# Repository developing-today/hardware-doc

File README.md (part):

# Hardware research

Standalone repository: **[`developing-today/hardware-doc`](https://github.com/developing-today/hardware-doc)**.

Device and component research, decomposed to primary evidence — netlists parsed from vendor
EDA files, firmware images unpacked, datasheets mined — with every claim carrying its source
and evidence status.

## How this repo is used

It is normally checked out **beside** the repo that consumes it and symlinked into place:

```
<repo-parent>/
├── code/                        consuming repo (config, infra, …)
│   └── doc/hardware  ───────────┐ symlink, created by scripts/hardware-doc-init.sh
├── hardware-doc/         ←──────┘ THIS REPO
└── repo-archive/        bulk artifacts moved out of here (separate repo, usually unpublished)
```

It is **not a submodule and not vendored** into the consuming repo: at ~440 MB it would
make every clone of that repo roughly 6.5× larger. Consumers clone it on demand.

```bash
git clone https://github.com/developing-today/hardware-doc.git
./scripts/init.sh        # only needed if the archive is not already a sibling
```

`scripts/init.sh` points `archive/` and `scratch/` at the sibling artifact archive. A fresh
clone usually needs nothing — the symlinks are committed relative, so they already resolve when
`repo-archive/` sits beside this repo. Run it when the archive is elsewhere, newly added, or
this repo is a linked worktree. It never clones and never deletes.

### Resolving the sibling archive

`../repo-archive` is a sibling of the **real repository root** — not of your working
directory, and not `~`. Under a git worktree resolve it via the *common* dir:

```bash
ARCHIVE="$(dirname "$(dirname "$(git rev-parse --path-format=absolute --git-common-dir)")")/repo-archive"
```

`--git-common-dir` rather than `--show-toplevel`: inside a linked worktree the toplevel is the
worktree, whose parent is the wrong directory. The archive holds bulky derived artifacts moved
out of this repo; every one leaves a `*.ARCHIVED.md` placeholder here carrying size, SHA-256,
upstream commit/author/licence and multiple recovery URLs, so **the archive is optional** —
its absence costs you convenience, not information.

`repo-archive` is **itself a git repository**, but it is normally **unpublished or
private** — at multiple gigabytes it is impractical to host alongside this one. Treat it as a
local companion: if you have it, placeholders resolve to real bytes; if you do not, they
resolve to recovery URLs.

### The `archive/` symlink

When the archive is present locally it is reachable at **`./archive/`** — a tracked symlink
into the `../repo-archive` repository. That gives `*.ARCHIVED.md` placeholders a stable in-repo
path to point at.

⚠ It resolves to **`../repo-archive/hardware-doc`** — the subdirectory named after **this
repository** — not to the archive root. `repo-archive` serves any sibling repo and namespaces
everything by source repo name, so the general form is `../repo-archive/<reponame>`; `scratch`
follows the same rule at `../repo-archive/scratch/<reponame>`.

So `archive/components/…` maps to `repo-archive/hardware-doc/components/…`, and a link written
`archive/hardware-doc/…` repeats the segment and **will not resolve** — silently, since a Markdown
link to a missing path just points at nothing.

Both tracked symlinks in this project (`archive` here, `doc/hardware` in a consuming repo)
are committed **relative**, and `hardware-doc-init.sh` swaps in an **absolute** path only
where the relative form cannot resolve — then marks the path `--skip-worktree`, because
`.gitignore` has no effect on tracked files. See
[`AGENTS.md` § Symlinks and `--skip-worktree`](AGENTS.md#symlinks-and---skip-worktree) for
the caveat that matters: while the flag is set, git will not update that path.

See [`AGENTS.md`](AGENTS.md) for working conventions and
[`.agents/skills/hardware-device-research/SKILL.md`](.agents/skills/hardware-device-research/SKILL.md)
for the research method.

- [Devices](devices/README.md)
- [Components and interfaces](components/README.md)
- [Vendor documentation-sourcing guides](vendors/README.md)
- [Cross-cutting guides](guides/README.md) — [Espressif](guides/espressif/README.md) · [hardware subsystems](guides/hardware/README.md) · [NFC](guides/nfc/README.md) · [LoRa](guides/lora/README.md) · [markets and sourcing](guides/markets/README.md) · [reverse engineering](guides/reverse-engineering/netlists-from-vendor-eda-files.md) · [research technique](guides/research/finding-projects-that-use-a-board.md) · [NixOS host](guides/nixos/README.md)
- [Artifact manifest](artifact-manifest.md)
- [Inventory](inventory.txt)
- [Verification report](verification.json)
- [Component download failures](component-download-failures.txt)

All research in this initial set was retrieved 2026-08-21. Downloaded files are checksummed from local bytes; see each device/component record for provenance and caveats. Relative-link validation covers authored Markdown outside `artifacts/`; bundled upstream Markdown is preserved as supplied and is not claimed to be link-clean.

- [Size audit](SIZE-AUDIT.md) — where the 442 MB is, what is reproducible, what must stay

## Research passes

| Pass | Date | Scope |
|---|---|---|
| Waveshare ESP32-S3-Knob-Touch-LCD-1.8 | 2026-08-21 → 2026-08-23 | One device, decomposed into ~22 component records; Espressif and Waveshare vendor guides created |
| Framework-guide extraction and archival | 2026-08-24 | Distilled ESP-IDF (×5 target builds), ESP-ADF, ESP-IoT-Solution and esp-dev-kits PDFs into [`guides/espressif/`](guides/espressif/README.md), then archived the ~219 MB of regenerable framework PDFs out of the repository. Chip datasheets, TRMs, errata, hardware-design guidelines and board design files were **all retained**. Per-directory archive records with SHA-256 and verified download URLs: [u4wdh](components/espressif/esp32-u4wdh/artifacts/ARCHIVED-FRAMEWORK-GUIDES.md) · [s3r8](components/espressif/esp32-s3r8/artifacts/ARCHIVED-FRAMEWORK-GUIDES.md) · [p4](components/espressif/esp32-p4/artifacts/ARCHIVED-FRAMEWORK-GUIDES.md) · [P4 boards](devices/espressif/shared-artifacts/ARCHIVED-FRAMEWORK-GUIDES.md) |
| **Espressif ESP32-P4 and its official development boards** | **2026-08-21** | [ESP32-P4 component record](components/espressif/esp32-p4/README.md) plus **five** board records under [devices/espressif/](devices/espressif/). Established the real P4 board lineup (no Korvo board exists on P4); corrected three claims in the [Espressif vendor guide](vendors/espressif/README.md#8-change-log-for-this-guide) |
| **Cross-link completion, vendor guides and market docs** | **2026-08-24** | **17 new [vendor sourcing guides](vendors/README.md)** (10 for manufacturers whose parts we document, 7 anticipatory), each with product lines, part-numbering conventions, distribution channels, URL patterns verified by live probe **with negative controls**, and an explicit evidence boundary. Added manufacturer back-links to every manufacturer-specific component record. New [markets and sourcing](guides/markets/README.md) guides and the [Espressif ecosystem map](guides/espressif/ecosystem-and-product-lines.md). **Corrected a WCH finding**: the `downloads/<PART>DS1_PDF.html` URLs return an identical 4,305-byte SPA shell for every path, existing or not |
| **Host toolchain: NixOS embedded development** | **2026-08-30** | New [`guides/nixos/`](guides/nixos/README.md) covering ESP-IDF on NixOS (5.5.2 and 6.0.1 side by side, and why installing the package alone yields no `idf.py`), package availability in the locked nixpkgs with dated absences, and why LVGL/sensor libraries are project dependencies. New [SquareLine vendor guide](vendors/squareline/README.md) — the Linux build is **a ZIP, not an AppImage**, and the CDN **returns HTTP 206 for non-existent paths**. The 172 MiB proprietary editor ZIP is archived out of the repository with a [reacquisition record](vendors/squareline/artifacts/ARCHIVED-SQUARELINE-STUDIO-LINUX.md). ⚠ **Nothing in this pass was built or rebuilt** |
| **Seven-session sweep: Xteink, M5Stack DinMeter / Cardputer / LoRa expansions, LilyGO K230 and T-Display-S3, LoRa generations** | **2026-09-04 → 2026-09-07** | ~40 device records and ~90 component records across seven parallel sessions, indexed here on 2026-09-07. New device families: [Xteink](devices/README.md#xteink-阅星瞳--星瞳-star-pupil) pocket e-readers (6), [LilyGO](devices/README.md#lilygo-shenzhen-xin-yuan-electronic-technology-also-trades-as-ttgo) (16, including the repository's **first RISC-V device**, the K230), and the expanded [M5Stack](devices/README.md#m5stack) family — DinMeter ×2, five Cardputers and eight Cardputer radio expansions. Three new vendor guides ([Canaan](vendors/canaan/README.md), [LilyGO](vendors/lilygo/README.md), [Semtech](vendors/semtech/README.md)) and three cross-cutting guides ([LoRa radio generations](guides/hardware/lora-radio-generations.md), [parallel 8080 LCD buses](guides/hardware/parallel-8080-lcd-buses.md), [RISC-V and vendor-SDK toolchains on NixOS](guides/nixos/riscv-and-vendor-sdk-toolchains.md)). ⚠ **Nothing in this pass was verified on physical hardware**, and each session was forbidden from editing shared indexes — the merge, its deferrals and its parked corrections are recorded in [`research/passes/index-merge/README.md`](research/passes/index-merge/README.md) |
| **Round two: Xteink re-survey, schematic net-tracing, certification and market** | **2026-09-11** | Three parallel sessions, integrated the same day. ⭐ **Overturned the sweep's Xteink certification finding**: Xteink holds **five FCC Original Equipment grants** under grantee code `2BTR9`, and enumerating that code surfaced a **sixth device the vendor has never announced** — the [X4 Light](devices/xteink/x4-light/README.md). Dated the **X4 Classic launch** (2026-09-06, USD 79) and the **X4's withdrawal**. **291 schematic PDFs assessed** and five boards net-traced from PDF alone — Altium exports embed `CO`/`PI`/`NL` tokens at item coordinates, which is what made it possible ([guide](guides/reverse-engineering/tracing-nets-from-schematic-pdfs.md)). **32 device records gained a `certification-and-compliance.md`**, each carrying its positive and negative controls. **174 FCC exhibits split**: 59 retained in-repo (57.8 MiB — internal photographs, including the **first public teardown of the Xteink X4**), 106 archived with self-sufficient placeholders (130.6 MiB); FCC exhibits are **US Government public records, redistribution `allowed`**. New guides: [finding certification records](guides/research/finding-certification-records.md), [tracing nets from schematic PDFs](guides/reverse-engineering/tracing-nets-from-schematic-pdfs.md); new [Xteink vendor guide](vendors/xteink/README.md). ⚠ **Still nothing verified on physical hardware.** ⚠ `devices/m5stack/papermono/**` was owned by a live session throughout and was **not touched** — its deferrals are in [`research/passes/index-merge/deferred-round2.md`](research/passes/index-merge/deferred-round2.md) |

| **Preprint repositories and the wider literature** | **2026-09-01 → 2026-09-11** | All 78 entries on Wikipedia's [List of preprint repositories][wpl] **plus what that list omits**, in [`research/preprint-repositories/`](research/preprint-repositories/README.md) — 40 records, ~23,000 lines. Deep records for the servers carrying hardware/software/systems work ([arXiv](research/preprint-repositories/arxiv.md), [Cryptology ePrint](research/preprint-repositories/cryptology-eprint-archive.md), [HAL](research/preprint-repositories/hal.md), [Zenodo](research/preprint-repositories/zenodo.md), [TechRxiv](research/preprint-repositories/techrxiv.md), [ECSarXiv](research/preprint-repositories/ecsarxiv.md)); grouped records for the rest. **160 landmark papers and theses individually verified** by fetching each identifier and machine-checking its title — [collected by field](research/preprint-repositories/landmark-papers.md). ⭐ **Corrected six Wikipedia claims by measurement** (OSF Preprints `>1,000,000` → **200,519** hosted; ScienceOpen → **~3,584**; [Synthical hosts nothing at all](research/preprint-repositories/synthical.md)). Extended beyond preprints to the [lawful full-text ladder](research/preprint-repositories/open-access-full-text-sources.md) (**USENIX has been paywall-free since 2008** — the real home of the systems literature), [government and university technical reports](research/preprint-repositories/government-and-institutional-technical-reports.md) (**the RISC-V ISA specs are six Berkeley EECS reports**, verified), the [computing servers Wikipedia omits](research/preprint-repositories/additional-preprint-servers.md) (**ECCC**, **OpenReview**), [theses and dissertations](research/preprint-repositories/theses-and-dissertations.md) (**the global ETD discovery layer collapsed in 2025–26**; EThOS is metadata-only since the British Library cyberattack), [dead-site recovery](research/preprint-repositories/recovering-dead-technical-sites.md) (**the DEC SRC/WRL/CRL series survives only as a 2007 bitsavers mirror**), and [bulk libraries and their copyright status](research/preprint-repositories/bulk-libraries-and-shadow-archives.md). ⚠ **No artifacts retained; no shadow-library service probed and no mirror domains recorded anywhere** |

[wpl]: https://en.wikipedia.org/wiki/List_of_preprint_repositories

## Quick entry points

- **How do I build firmware from this machine?** — [NixOS as an embedded development host](guides/nixos/README.md)
- **Where is the paper for this, and can I trust it?** — [preprint repositories](research/preprint-repositories/README.md) · [landmark papers by field](research/preprint-repositories/landmark-papers.md) · [reliability and durability](research/preprint-repositories/reliability-and-durability.md)
- **I have a citation and want the PDF, legally** — [open-access full-text ladder](research/preprint-repositories/open-access-full-text-sources.md)
- **A vendor doc portal or datasheet host has died** — [recovering dead technical sites](research/preprint-repositories/recovering-dead-technical-sites.md)

- **Which Espressif chip should this be?** — [ecosystem and product lines](guides/espressif/ecosystem-and-product-lines.md)
- **Which of these boards should I use?** — [device comparison matrix](guides/markets/device-comparison-matrix.md) — all fourteen documented devices side by side
- **How many PCNT units / DMA channels / UARTs does this chip have?** — [SoC peripheral reference](guides/espressif/soc-peripheral-reference.md)
- **How do I drive this display?** — [display interfaces](guides/hardware/display-interfaces.md) · e-paper specifically — [e-paper displays](guides/hardware/e-paper-displays.md)
- **How do I bring up an NFC reader, and why does it read nothing?** — [NFC guide](guides/nfc/README.md) — standards, antenna matching, and symptom-to-cause debugging
- **What do SF, BW and CR actually cost me?** — [LoRa guide](guides/lora/README.md) — airtime, battery and duty-cycle arithmetic, LoRa vs LoRaWAN vs Meshtastic, and honest range estimation
- **Where should I buy this, and will the docs survive?** — [vendor and marketplace comparison](guides/markets/vendor-comparison.md)
- **Is this board a clone, and what differs?** — [clones, siblings and variants](guides/markets/clones-and-variants.md)
- **How do I recover a pinout the vendor never published?** — [netlists from vendor EDA files](guides/reverse-engineering/netlists-from-vendor-eda-files.md)
- **Espressif ESP32-P4** — [chip](components/espressif/esp32-p4/README.md) · [board index](devices/README.md#espressif--official-esp32-p4-development-boards) · [shared board artifacts](devices/espressif/shared-artifacts/README.md)
- **Espressif ESP32-S3** — [ESP32-S3R8](components/espressif/esp32-s3r8/README.md), including the [Bluetooth Classic limitation](components/espressif/esp32-s3r8/README.md#radio-capabilities-and-the-classic-bluetooth-limitation)
- **How to obtain any Espressif document** — [vendor guide](vendors/espressif/README.md)
- **Espressif framework knowledge** — [ESP-IDF peripheral capabilities](guides/espressif/esp-idf-peripheral-capabilities.md) · [ESP-ADF audio pipelines](guides/espressif/esp-adf-audio-pipelines.md) · [ESP-IoT-Solution components](guides/espressif/esp-iot-solution-components.md)
- **Which LoRa chip is this, and what breaks if I swap it?** — [LoRa radio generations](guides/hardware/lora-radio-generations.md) — the four generations of Semtech silicon, and the migration cost. ⚠ The **LLCC68 is pin-compatible with the SX1262 and 19 dB worse**; the **SX1268 cannot reach 868/915 MHz** at all
- **My display is black and the library says it initialised** — [parallel Intel-8080 LCD buses on ESP32](guides/hardware/parallel-8080-lcd-buses.md) — why the display-library choice matters more than the board, and a debugging checklist
- **How do I build for a RISC-V board with a vendor SDK?** — [RISC-V and vendor-SDK toolchains on NixOS](guides/nixos/riscv-and-vendor-sdk-toolchains.md) — why `pkgsCross.riscv64-*` is not a substitute for XuanTie GCC
- **I want a cheap pocket e-reader I can reflash** — [Xteink family](devices/README.md#xteink-阅星瞳--星瞳-star-pupil) — six products, four ESP32-based. ⚠ **The X4 Pro is not an enhanced X4**; firmware for one will not run on the other
- **Which LilyGO T-Display-S3 is this actually?** — [LilyGO family index](devices/README.md#lilygo-shenzhen-xin-yuan-electronic-technology-also-trades-as-ttgo) — one *name* covering eleven boards, eight display controllers and four chargers. Sourcing: [LilyGO vendor guide](vendors/lilygo/README.md)
- **How do I add LoRa, sub-GHz or NFC to a Cardputer?** — [M5Stack Cardputer expansions](devices/README.md#cardputer-expansions--lora-sub-ghz-and-nfc--added-2026-09-04) — and note that only the **ADV + Cap LoRa-1262** combination has an upstream Meshtastic variant
- **How do I obtain a Semtech, Canaan or LilyGO document?** — [Semtech](vendors/semtech/README.md) · [Canaan](vendors/canaan/README.md) · [LilyGO](vendors/lilygo/README.md) vendor guides
- **Is this thing certified, and how would I even check?** — [finding certification records](guides/research/finding-certification-records.md) — FCC grantee-code enumeration, which regulatory databases are actually reachable, and **the positive/negative controls that make an absence finding mean anything**. ⚠ `fccid.io` serves **403 to a Chrome UA and 200 to `curl`** — the honest user agent is the one that works
- **The vendor published a schematic PDF and nothing else** — [tracing nets from schematic PDFs](guides/reverse-engineering/tracing-nets-from-schematic-pdfs.md) — Altium exports embed invisible `CO`/`PI`/`NL` tokens at item coordinates, which is what makes a net list recoverable with poppler alone. ⚠ **KiCad and EAGLE exports often outline their text to vector paths** and are then untraceable — but a usable second export often sits in the same directory
- **What has this vendor certified that it never announced?** — [Xteink vendor guide](vendors/xteink/README.md) — the worked example: enumerating grantee code `2BTR9` surfaced the [X4 Light](devices/xteink/x4-light/README.md), a device with no announcement, no listing and no price

## Verification reports

- [Preprint and scholarly-literature repositories](research/preprint-repositories/VERIFICATION.md) — 2026-09-11 re-probe of a 2026-09-01 → 07 pass: 40 records, 78/78 list coverage, 160 identifiers verified, 0 broken links. **Five findings corrected** (Berkeley EECS restored at a new path; Anubis answers HTTP 200 not 403; CERN CDS and ETH no longer walled; OpenReview's API block was transient; CogPrints' recovery route degraded) and **one dating error flagged**.
- [Seeed XIAO ESP32S3 Sense](VERIFICATION-xiao-esp32s3-sense.md) — 2026-08-24: 1,092 files, 42 artifacts validated, 0 broken links, 0 hardware-tested claims.
- [M5Stack PaperMono](VERIFICATION-m5stack-papermono.md) — 2026-09-01: 50 authored files (~14,700 lines), 23 artifacts validated, 0 broken links, 0 hardware-tested claims; 5 hypotheses refuted, 10 conflicts left open.
- [**Seven-session device sweep**](VERIFICATION-sweep-2026-09-04.md) — 2026-09-04 → 2026-09-07: the umbrella report for the whole pass. 469 authored files, **10 387 relative links checked / 1 broken** (pre-existing, in a vendored upstream README), 61 artifacts magic-byte validated / 0 mismatches, 0 device-record orphans, 0 deletions on any shared file, `HEAD` unchanged. ⚠ **Zero on-device claims.**
- [Xteink device family](VERIFICATION-xteink.md) — 2026-09-04: Xteink X3, X4, X4 Pro, X4 Classic, S4 and Nano.
- [M5Stack DinMeter](VERIFICATION-m5stack-dinmeter.md) — 2026-09-04: DinMeter (K134) and DinMeter v1.1 (K134-V11).
- [M5Stack Cardputer family](VERIFICATION-m5stack-cardputer.md) — 2026-09-04: 48 authored files, 331/331 links, 6/6 artifact hashes, 0 protected files touched.
- [LilyGO T-Display K230](VERIFICATION-lilygo-t-display-k230.md) — 2026-09-04: T-Display K230 and K230 Kit, the repository's first RISC-V device.
- [**Xteink family, round two**](VERIFICATION-xteink-round2.md) — 2026-09-11: the **X4 Classic launch** at USD 79 and the X4's withdrawal, the **undocumented X4 Light** found by FCC grantee enumeration, and three new custodians for the X4 Pro.
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
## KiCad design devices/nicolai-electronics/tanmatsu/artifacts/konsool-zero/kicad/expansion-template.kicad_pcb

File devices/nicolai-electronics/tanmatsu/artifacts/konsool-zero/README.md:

# `konsool-zero` — KiCad EDA source

The complete published design of **`badgeteam/konsool-zero`**, the Flipper-Zero-class RFID / NFC /
sub-GHz / iButton / IR add-on for the Tanmatsu rear 36-pin port.

**These files are the evidence** behind the fitment findings and the STM32WB55CC correction in
[`../../expansion-boards.md` §2](../../expansion-boards.md), and behind the full connector wiring
and host GPIO map in [`../../konsool-zero-wiring.md`](../../konsool-zero-wiring.md). Before this
pass they existed only in `scratch/`, which meant the corrections cited evidence that was not in
the repository.

## Identity

| Field | Value |
|---|---|
| Upstream repository | <https://github.com/badgeteam/konsool-zero> |
| Commit | **`0f0b964107c15dd398ee3e44a064fb853b17aaa8`** |
| Commit subject | *"board elements that were missing."* |
| Author | Paul Honig `<paul@etv.cx>` |
| Committed | **2025-03-22T11:38:10+01:00** |
| Tag / release | **none** — the repository has exactly **one commit** and no releases |
| Retrieved | **2026-08-26** (clone), filed here **2026-09-20** |
| Licence | **BSD 3-Clause, Copyright (c) 2024, Nicolai Electronics** — see `LICENSE-BSD-3-Clause` |
| Redistribution status | `allowed` (BSD-3-Clause), with the attribution and non-endorsement conditions |
| Disposition | `repository` |
| Upstream README | **none** — the repository ships no README |

> ⚠ **Correction, 2026-09-20.** [`../../expansion-boards.md`](../../expansion-boards.md) previously
> recorded this project's licence as *"none stated"* in §1 and *"no stated licence"* in §2. That was
> wrong: a `LICENSE` file **is** tracked at `0f0b964` and carries the BSD 3-Clause text above.
> Both statements have been corrected. The *"no README"* and *"one commit"* claims were checked and
> are **correct**.

## Contents

| Path | Bytes | What it is |
|---|---:|---|
| `kicad/tanmantsu-zero.kicad_pcb` | 2 391 120 | **The authoritative artifact** — PCB with resolved net names on every pad |
| `kicad/tanmantsu-zero.kicad_sch` | 89 740 | Root sheet *(upstream misspelling of "tanmatsu" preserved)* |
| `kicad/tanmantsu-zero.kicad_pro` | 21 097 | Project file |
| `kicad/zero-mcu.kicad_sch` | 62 270 | CH32V003F4U6 (`U19`) and its 25 MHz oscillator |
| `kicad/sub-ghz-radio.kicad_sch` | 71 725 | CC1101RGPR (`U1`), 27 MHz XO (`U2`) |
| `kicad/nfc-block.kicad_sch` | 134 986 | ST25R3916-AQWT (`U5`), 27.12 MHz crystal (`X1`) |
| `kicad/rfid-schematic.kicad_sch` | 208 383 | 125 kHz analog front end |
| `kicad/antenna-balance.kicad_sch` | 74 073 | SP3T switches `U3`/`U4`, band matching |
| `kicad/rf-balance.kicad_sch` | 35 098 | CC1101 balun network |
| `kicad/ir-comms.kicad_sch` | 52 737 | TSOP75338 receiver, three VSMY14940 emitters |
| `kicad/ibutton.kicad_sch` | 12 494 | 1-Wire contact and TVS |
| `kicad/expansion-template.kicad_sch` | 81 314 | **Shared add-on outline template** — see below |
| `kicad/expansion-template.kicad_pcb` | 543 022 | konsool-zero's layout of that template |
| `kicad/fp-lib-table`, `kicad/sym-lib-table` | 425 / 131 | Library tables |
| `kicad/pcb_coils/COIL_GENERATOR.kicad_mod` | 117 869 | Parametric spiral coil footprint |
| `kicad/pcb_coils/COIL_RFID_ZERO.kicad_mod` | 117 869 | The 125 kHz RFID coil as laid out |
| `LICENSE-BSD-3-Clause` | 1 506 | Upstream `LICENSE`, renamed for clarity |

### The expansion template is shared by copy

`kicad/expansion-template.kicad_sch` is **byte-identical** to
`konsool-18650-expansion/expansion-template.kicad_sch`
(`fa79df7fc3988227bebae85eccb74a694b47a6fd14ca758553906ad9f4636dd1`). The
`badgeteam/konsool-expansion-template` repository that was supposed to hold it is
empty, so add-on designers copy this file between projects by hand. See
[`../../konsool-zero-wiring.md` §9](../../konsool-zero-wiring.md).

⚠ It inherits konsool-zero's **pin-7 `VSDCARD` mislabel** (pin 7 is `GND` on the Tanmatsu) and its
**wrong `E8`/`E9`/`E10` names**. Check against
[`../../pinouts-and-buses.md` §2](../../pinouts-and-buses.md) before reusing it.

## Not copied here

| Left in scratch | Why |
|---|---|
| `library/lcsc.3dshapes/` (~68 MB, 42 STEP + WRL pairs) | Generic LCSC package meshes — not board-specific, regenerable from upstream, carry no electrical information |
| `jlcpcb/project.db` (20 480 B) | SQLite cache written by the JLCPCB fabrication-toolkit plugin; a build artifact |
| `docs/` chip datasheets (7 PDFs) | **Component** artifacts — filed under `components/` by the 2026-09-20 pass and removed from the clone. See [`../../sources.md`](../../sources.md) |
| `docs/*.pdf` — six Flipper Devices schematics | Describe a **different product**; filed under [`devices/flipper-devices/flipper-zero/`](../../../../flipper-devices/flipper-zero/README.md) |
| `docs/flipper-zero-photos/` (4.0 MB) | Filed with the Flipper record and archived — see that record's placeholder |

## Re-acquisition

```bash
git clone https://github.com/badgeteam/konsool-zero
git -C konsool-zero checkout 0f0b964107c15dd398ee3e44a064fb853b17aaa8
sha256sum konsool-zero/tanmantsu-zero.kicad_pcb
# expect 21eb0005720cc0a20a2e169e72ef80b4773010b4f14b14afdbce874b8e0e3b2d
```

⚠ The repository has **no `main` branch** — a `raw.githubusercontent.com/.../main/...` URL 404s
(recorded in [`../../commands.md`](../../commands.md)). Always use the pinned commit.

Reacquisition status: **automatic**. Hashes verified against the local checkout on 2026-09-20;
the GitHub endpoint was **not** re-probed in this pass.

## Why these are copies, not moves

`scratch/tanmatsu/sources/konsool-zero/` remains a working KiCad project so the parsers can be
re-run against it. Every file here was verified **byte-identical by SHA-256** to its scratch
counterpart at the moment of copying. The scratch clone is already `dirty` — the 2026-09-20 pass
*moved* the seven chip datasheets out of `docs/` when filing them as component artifacts — so
`git status` there reports seven deletions by design.

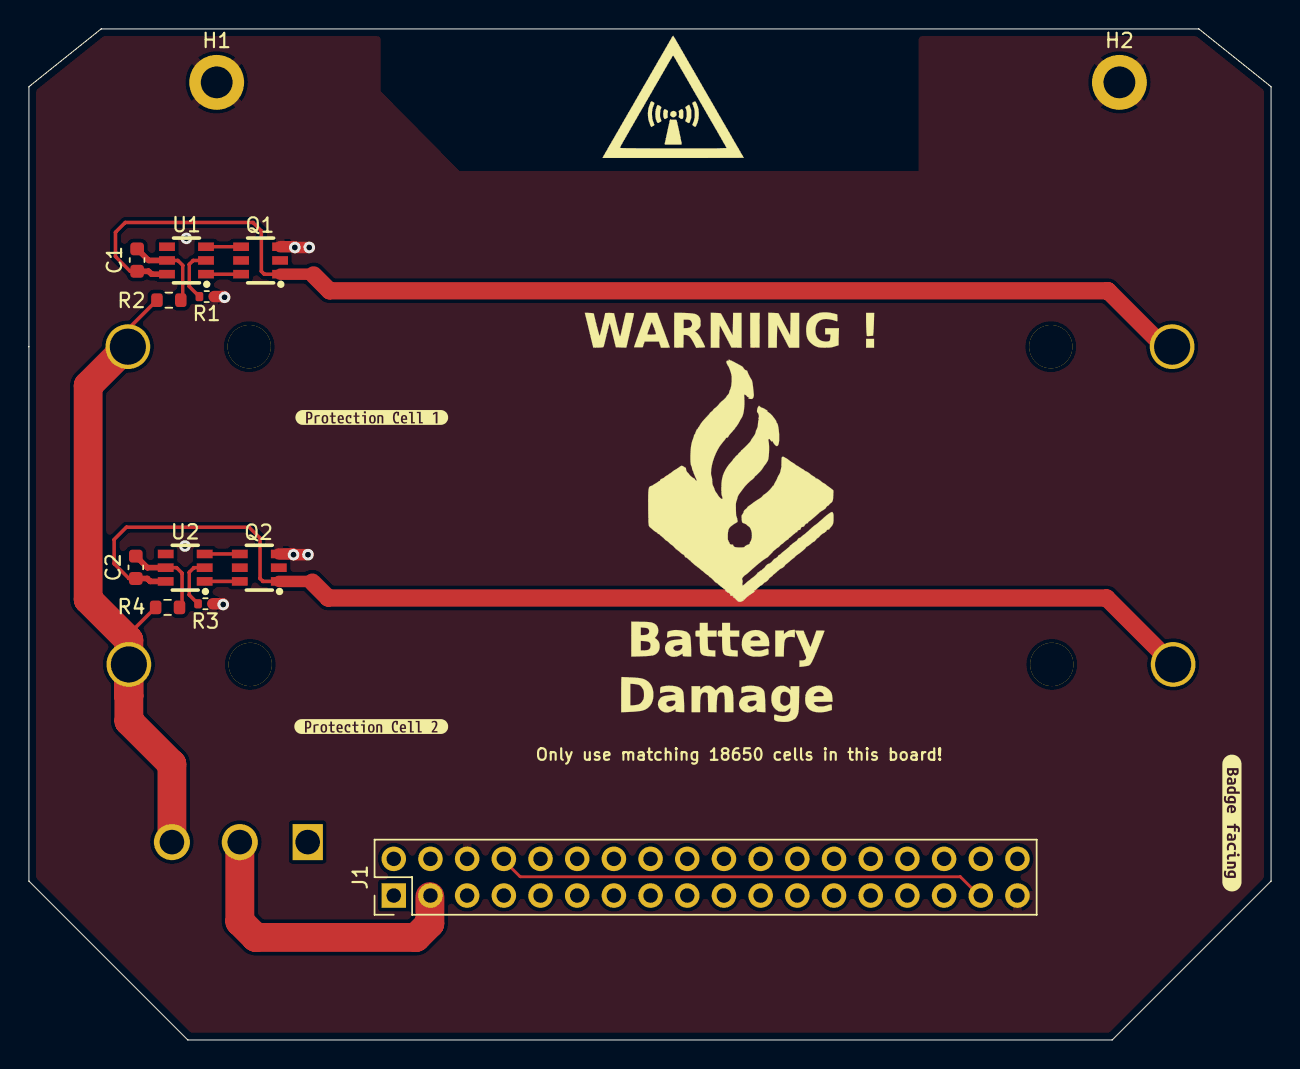
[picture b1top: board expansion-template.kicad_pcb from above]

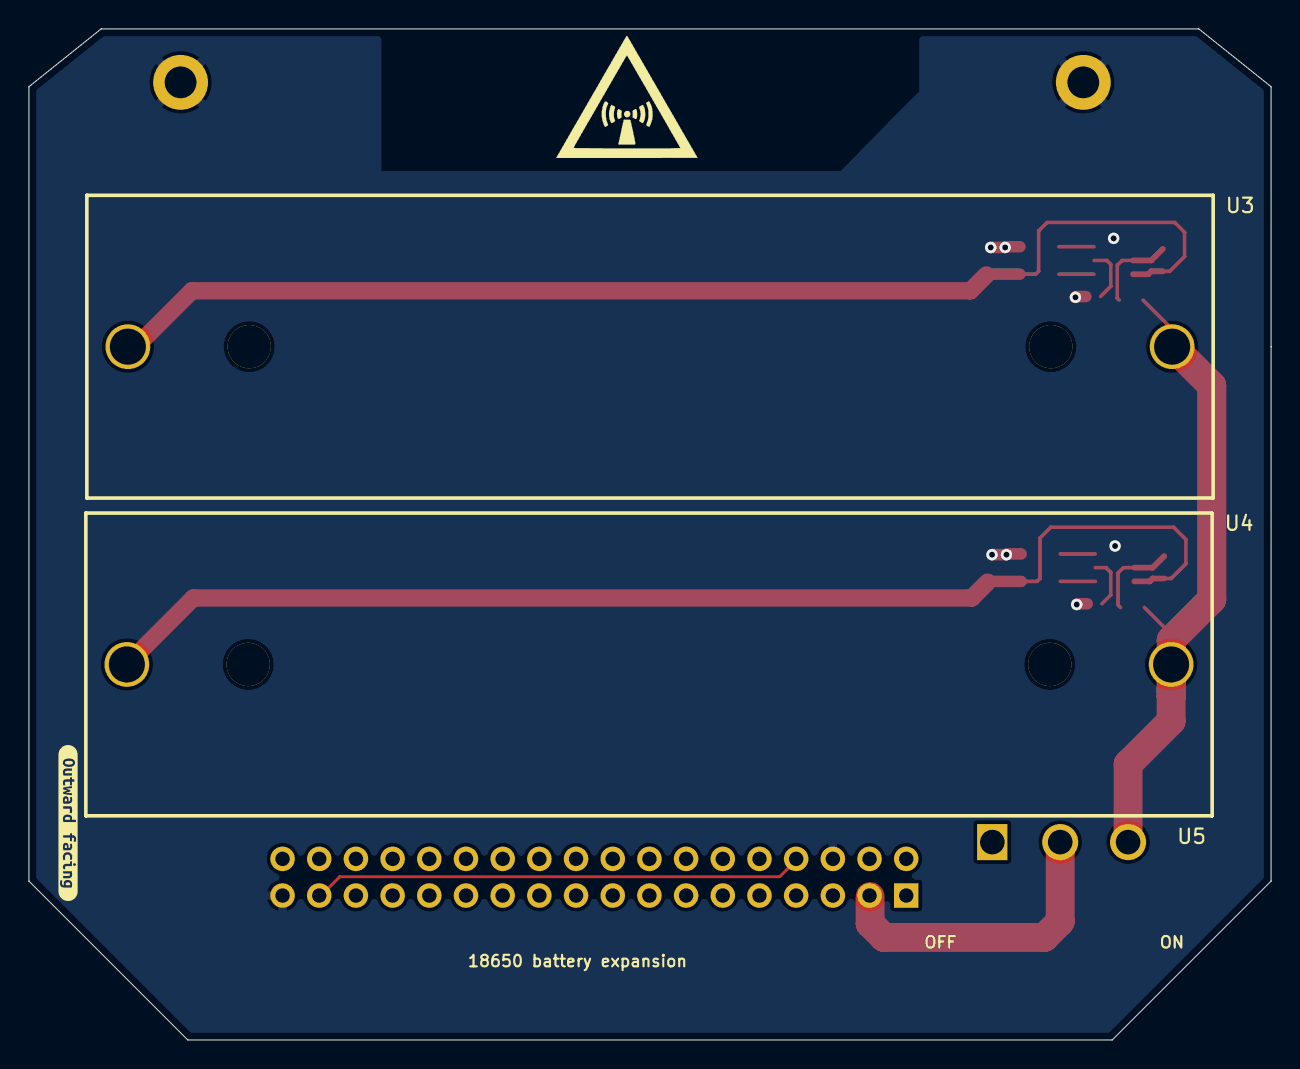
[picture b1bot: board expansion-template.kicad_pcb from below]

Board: 2 copper layers, 86.0 x 70.0 mm, 24 parts (5 on the bottom side), 14 nets.

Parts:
C1, C2: 82nF; C_0603_1608Metric
H1, H2: Mounting hole; MountingHole_2.2mm_M2_DIN965_Pad
J1: Internal Add-On; PinHeader_2x18_P2.54mm_Vertical
N1: Board-outline; why2025-mainboard-edge-cuts-usr
N2, N4: Radio-logo; radio_logo
N3: LiPo-police; Battery-damage
Q1, Q2: FS8205A_C2830320; SOT-23-6_L2.9-W1.6-P0.95-LS2.8-BR
R1, R3: 1k; R_0402_1005Metric
R2, R4: 100; R_0603_1608Metric
U1, U2: DW01A; SOT-23-6_L2.9-W1.6-P0.95-LS2.8-BR
U3, U4: BH-18650-A5BJ001-2D; BAT-TH_BH-18650-A5BJ001-2D
U5: SS-12D06-G050; SW-TH_3P-P4.70_SS-12D06-G050
kibuzzard-672F9ADC: G***; kibuzzard-672F9ADC
kibuzzard-672F9AF8: G***; kibuzzard-672F9AF8
kibuzzard-672F417C: G***; kibuzzard-672F417C
kibuzzard-672F4776: G***; kibuzzard-672F4776

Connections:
+3.3V: J1.8, J1.33
/CELL1/VBATT: R2.2, R4.2, U3.1, U4.1, U5.3
GND: H1.1, H2.1, J1.6, J1.35, Q1.3 (S2), Q2.3 (S2), R1.1, R3.1
unnamed: Q1.6 (G1), U1.1 (OD)
unnamed: Q1.4 (G2), U1.3 (OC)
unnamed: C1.2, Q1.1 (S1), U1.6 (GND), U3.2
unnamed: Q2.6 (G1), U2.1 (OD)
unnamed: Q2.4 (G2), U2.3 (OC)
unnamed: C2.2, Q2.1 (S1), U2.6 (GND), U4.2
unnamed: R1.2, U1.2 (CS)
unnamed: C1.1, R2.1, U1.5 (VCC)
unnamed: R3.2, U2.2 (CS)
unnamed: C2.1, R4.1, U2.5 (VCC)
VBATT: J1.3, U5.2

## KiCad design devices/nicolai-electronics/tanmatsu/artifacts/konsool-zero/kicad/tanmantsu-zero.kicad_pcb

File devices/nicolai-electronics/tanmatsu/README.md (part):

# Nicolai Electronics Tanmatsu

> "The terminal for hackers" — an ESP32-P4 handheld with a QWERTY keyboard, LoRa, MIPI DSI display and a 36-pin expansion port.
> Manufacturer: **Nicolai Electronics** (Netherlands) · Designer: **Renze Nicolai** with **Paul Honig**
> Research snapshot **2026-08-24** · Hardware repo commit `640805dd` (2026-02-25)

Tanmatsu is a conference-badge-derived, commercially sold handheld computer. It sits in the lineage of the Dutch hacker-camp badges (MCH2022, WHY2025) built by [Badge.team](https://badge.team), but is a product in its own right rather than an event giveaway.

**It is unusually well documented for a custom board, and unusually open**: the full KiCad design is published under **CERN-OHL-P**, the firmware under **MIT**, and there is a Sphinx documentation site maintained in git. The limiting factor on information is not secrecy — it is that the device is new, low-volume, and much of the detail is spread across ~10 repositories rather than being absent.

---

## Common tasks / How do I…?

| Question | Answer |
|---|---|
| What chips are on it? | [§ Architecture](#architecture-three-processors) · [`bom.md`](bom.md) |
| **How does the keyboard work? / I have spare keyboards** | [`keyboard.md`](keyboard.md) — matrix, keymap, I2C, and the Solder Party family |
| **How does the display work?** | [`display.md`](display.md) |
| **How do I build an add-on / front panel?** | [`expansion-boards.md`](expansion-boards.md) |
| **I'm wiring something to the 36-pin port — what are the real GPIOs?** | [`konsool-zero-wiring.md`](konsool-zero-wiring.md) — a worked add-on, pin by pin, **and three naming traps** |
| **What does it cost? How big is it?** | [`pricing-and-dimensions.md`](pricing-and-dimensions.md) |
| **How does BadgeLink / AppFS work internally?** | [`badgelink-and-appfs.md`](badgelink-and-appfs.md) |
| **How is the software architected? How do I add an app?** | [`software-architecture.md`](software-architecture.md) |
| **How do I *build* an app vs a plugin?** | [`apps-vs-plugins.md`](apps-vs-plugins.md) |
| **Custom `.bin` vs installing an app? How does an app get executed?** | [`apps-vs-plugins.md` §8–9](apps-vs-plugins.md) |
| **Does this need a P4? A dual-chip setup?** | [`portability.md`](portability.md) — **no** to both |
| What is on the expansion ports? | [`pinouts-and-buses.md`](pinouts-and-buses.md) |
| How do I flash / recover it? | [`development.md`](development.md) |
| How do I write an app? | [`development.md`](development.md) · [`software-and-apps.md`](software-and-apps.md) |
| What apps exist already? | [`software-and-apps.md`](software-and-apps.md) — 57 catalogued |
| **What is "Konsool"?** | [`konsool-and-family.md`](konsool-and-family.md) — **answered** |
| What is unresolved or contradictory? | [`gaps-and-conflicts.md`](gaps-and-conflicts.md) |
| Where did all this come from? | [`sources.md`](sources.md) |

---

## Identity: Tanmatsu, Konsool and WHY2025

Three names appear throughout the software and they are **not** interchangeable in the way you might assume:

| Name | What it is |
|---|---|
| **Tanmatsu** | The commercial product sold by Nicolai Electronics. 端末 (*tanmatsu*) is Japanese for "terminal / handheld device". |
| **Konsool** | A sibling device. The app repository states plainly: *"Since Tanmatsu and Konsool are essentially the same device we recommend always adding both to apps developed for one of these boards."* Firmware treats them as separate build targets (`CONFIG_BSP_TARGET_TANMATSU` / `CONFIG_BSP_TARGET_KONSOOL`) that share almost all code. |
| **WHY2025** | The badge for the WHY2025 hacker camp. A third BSP target (`CONFIG_BSP_TARGET_WHY2025`) sharing the same code paths. |

In the badge BSP the three appear together in the same `#if defined(...)` guards, e.g. in [`esp32-component-tanmatsu-wifi/wifi_remote.c`](artifacts/source-snapshots/):

```c
#if defined(CONFIG_BSP_TARGET_TANMATSU) || defined(CONFIG_BSP_TARGET_KONSOOL) || defined(CONFIG_BSP_TARGET_WHY2025)
```

**Practical consequence:** software written for one generally runs on the others, and app authors are asked to declare multiple targets. Of the 57 apps in the official repository, **54 declare `tanmatsu`, 43 declare `konsool`, and only 4 declare `why2025`** — so the Tanmatsu/Konsool pair is the real ecosystem.

> The exact commercial and organisational relationship between the three names — and why a second name exists at all — is **not explained in any repository or document I retrieved**. See [`gaps-and-conflicts.md`](gaps-and-conflicts.md). I am deliberately not repeating community speculation about naming disputes as fact.

---

## Key specifications

| | |
|---|---|
| **Application processor** | **Espressif ESP32-P4NRW32** — dual-core 32-bit RISC-V, **32 MB in-package PSRAM** |
| Clock | **360 MHz or 400 MHz — the vendor's own docs disagree**, see [`gaps-and-conflicts.md`](gaps-and-conflicts.md) |
| **Flash** | **Winbond W25Q128JVS**, 16 MB (128 Mbit), SOIC-8 |
| **Radio module** | **Espressif ESP32-C6-WROOM-1-N8** — RISC-V @160 MHz, 512 KB RAM, 8 MB flash. Wi-Fi 6 (2.4 GHz), BLE 5.3, IEEE 802.15.4 (Thread 1.3 / Zigbee 3.0) |
| **Coprocessor** | **WCH CH32V203C8T6** — RISC-V @144 MHz, 20 KB RAM, 64 KB flash, LQFP-48 |
| **LoRa** | **Ebyte E22-900M22S** (868/915 MHz) or **E22-400M22S** (433 MHz). 22 dBm |
| **Display** | **SWI LH397K-IC01**, 3.97", 480×800, RGB565, **ST7701S** controller, **MIPI DSI 2-lane**, 330 cd/m² |
| **Keyboard** | 69-key QWERTY + 6 coloured function keys, metal dome sheet, white LED backlight. Designed by **Solder Party** |
| **Battery** | 2500 mAh LiPo, 3.7 V nominal, "104050", JST PH-2.0 (Adafruit-compatible), Tewaycell |
| **Audio** | **ES8156** stereo DAC/codec + **FM8002A** mono amp → 8 Ω speaker; 3.5 mm jack |
| **PMIC** | **TI BQ25895RTW** — charger, monitoring, 5 V boost |
| **3.3 V rail** | **TI TPS63020DSJR** buck-boost |
| **IMU** | **Bosch BMI270** accel + gyro |
| **LEDs** | 6 × **SK6805-EC20** addressable |
| **USB** | **CH334R** 4-port hub; USB-C device + USB-A host (1 A, current limited) |
| **Storage** | microSD, SDIO 2.0/3.0, **3.3 V and 1.8 V** signalling |
| **Camera** | 22-pin MIPI CSI, Raspberry Pi Zero/5 pinout compatible |
| **Case** | 3D printed, **120 × 135 × 18 mm**, **215 g** with battery |
| **Mainboard PCB** | **~114.9 mm wide** — *measured from `tanmatsu.step`, not vendor-published*. See [`pricing-and-dimensions.md`](pricing-and-dimensions.md) |
| **Price** | **€99.17** ex VAT / **€119.99** inc 21% NL VAT (2026-08-24) |

Full reference-designator BOM with LCSC part numbers: [`bom.md`](bom.md) · raw [`artifacts/production/bom.csv`](artifacts/production/bom.csv)

---

## Architecture: three processors

Tanmatsu is not a single-MCU board. Three processors run concurrently, each owning a distinct domain.

```
                    ┌──────────────────────────────────────────┐
   USB-C ──► CH334R │  ESP32-P4 (U7)  dual RISC-V, 32MB PSRAM  │
      hub  ─┬──────►│  application processor · 16MB W25Q128    │
            │       │  MIPI DSI display · MIPI CSI camera      │
            │       │  SDIO · I2S · I3C · USB OTG ×2 PHY       │
            │       └───────┬──────────────────────────────────┘
            │          internal I2C (GPIO9 SDA / GPIO10 SCL)
            │               │
            │       ┌───────▼──────────────────────────────────┐
            │       │  CH32V203C8T6 (U12) @0x5F                │
            │       │  keyboard matrix scan · RTC (32.768kHz)  │
            │       │  backlight PWM ×2 · PMIC control         │
            │       │  power sequencing · SK6805 LEDs          │
            │       │  headphone detect · USB-A power switch   │
            │       └───────┬──────────────────────────────────┘
            │           PMIC I2C │  BQ25895 @0x6A
            │                    ▼
            └──────►┌──────────────────────────────────────────┐
                    │  ESP32-C6-WROOM-1 (U20)                  │
                    │  Wi-Fi 6 / BLE 5.3 / 802.15.4            │
                    │  runs esp-hosted — a *radio peripheral*, │
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
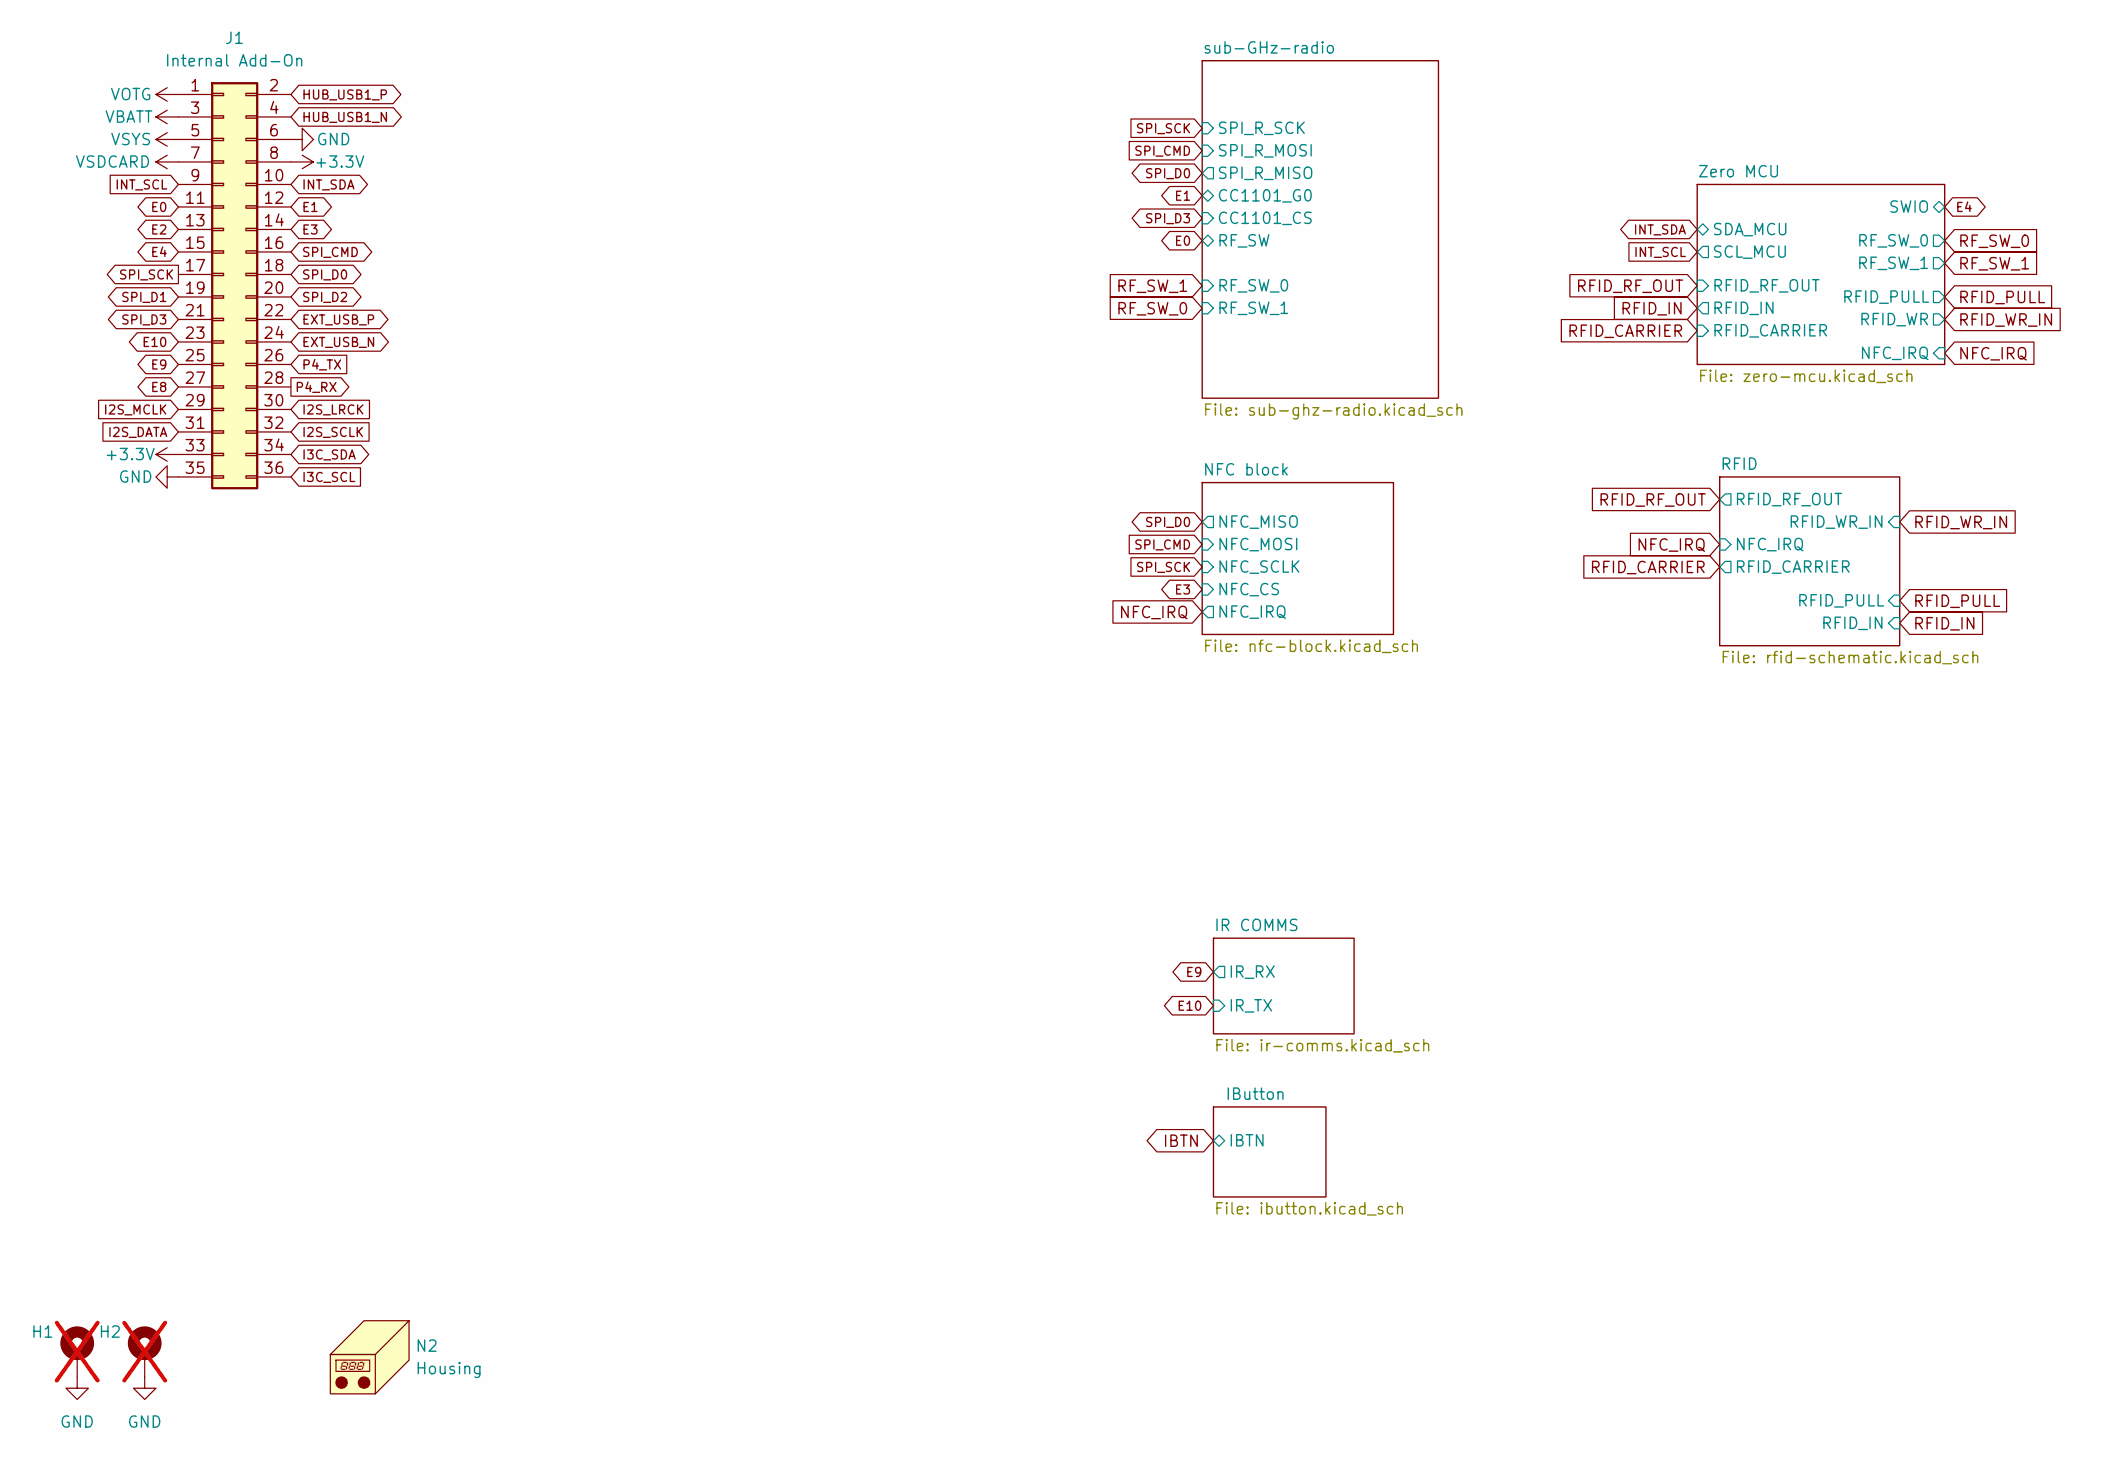
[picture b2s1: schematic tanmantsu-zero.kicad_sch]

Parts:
H1, H2: Mounting hole; MountingHole_2.2mm_M2_DIN965_Pad; not fitted
J1: Internal Add-On; PinHeader_2x18_P2.54mm_Vertical; LCSC C168945
N2: Housing; boards-guide

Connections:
+3.3V: J1.8, J1.33; also elsewhere on the board
E0: J1.11; also elsewhere on the board
E1: J1.12; also elsewhere on the board
E2: J1.13
E3: J1.14; also elsewhere on the board
E4: J1.15; also elsewhere on the board
E8: J1.27
E9: J1.25; also elsewhere on the board
E10: J1.23; also elsewhere on the board
EXT_USB_N: J1.24
EXT_USB_P: J1.22
GND: H1.1, H2.1, J1.6, J1.35; also elsewhere on the board
HUB_USB1_N: J1.4
HUB_USB1_P: J1.2
I2S_DATA: J1.31
I2S_LRCK: J1.30
I2S_MCLK: J1.29
I2S_SCLK: J1.32
I3C_SCL: J1.36
I3C_SDA: J1.34
INT_SCL: J1.9; also elsewhere on the board
INT_SDA: J1.10; also elsewhere on the board
P4_RX: J1.28
P4_TX: J1.26
SPI_CMD: J1.16; also elsewhere on the board
SPI_D0: J1.18; also elsewhere on the board
SPI_D1: J1.19
SPI_D2: J1.20
SPI_D3: J1.21; also elsewhere on the board
SPI_SCK: J1.17; also elsewhere on the board
VBATT: J1.3
VOTG: J1.1
VSDCARD: J1.7
VSYS: J1.5

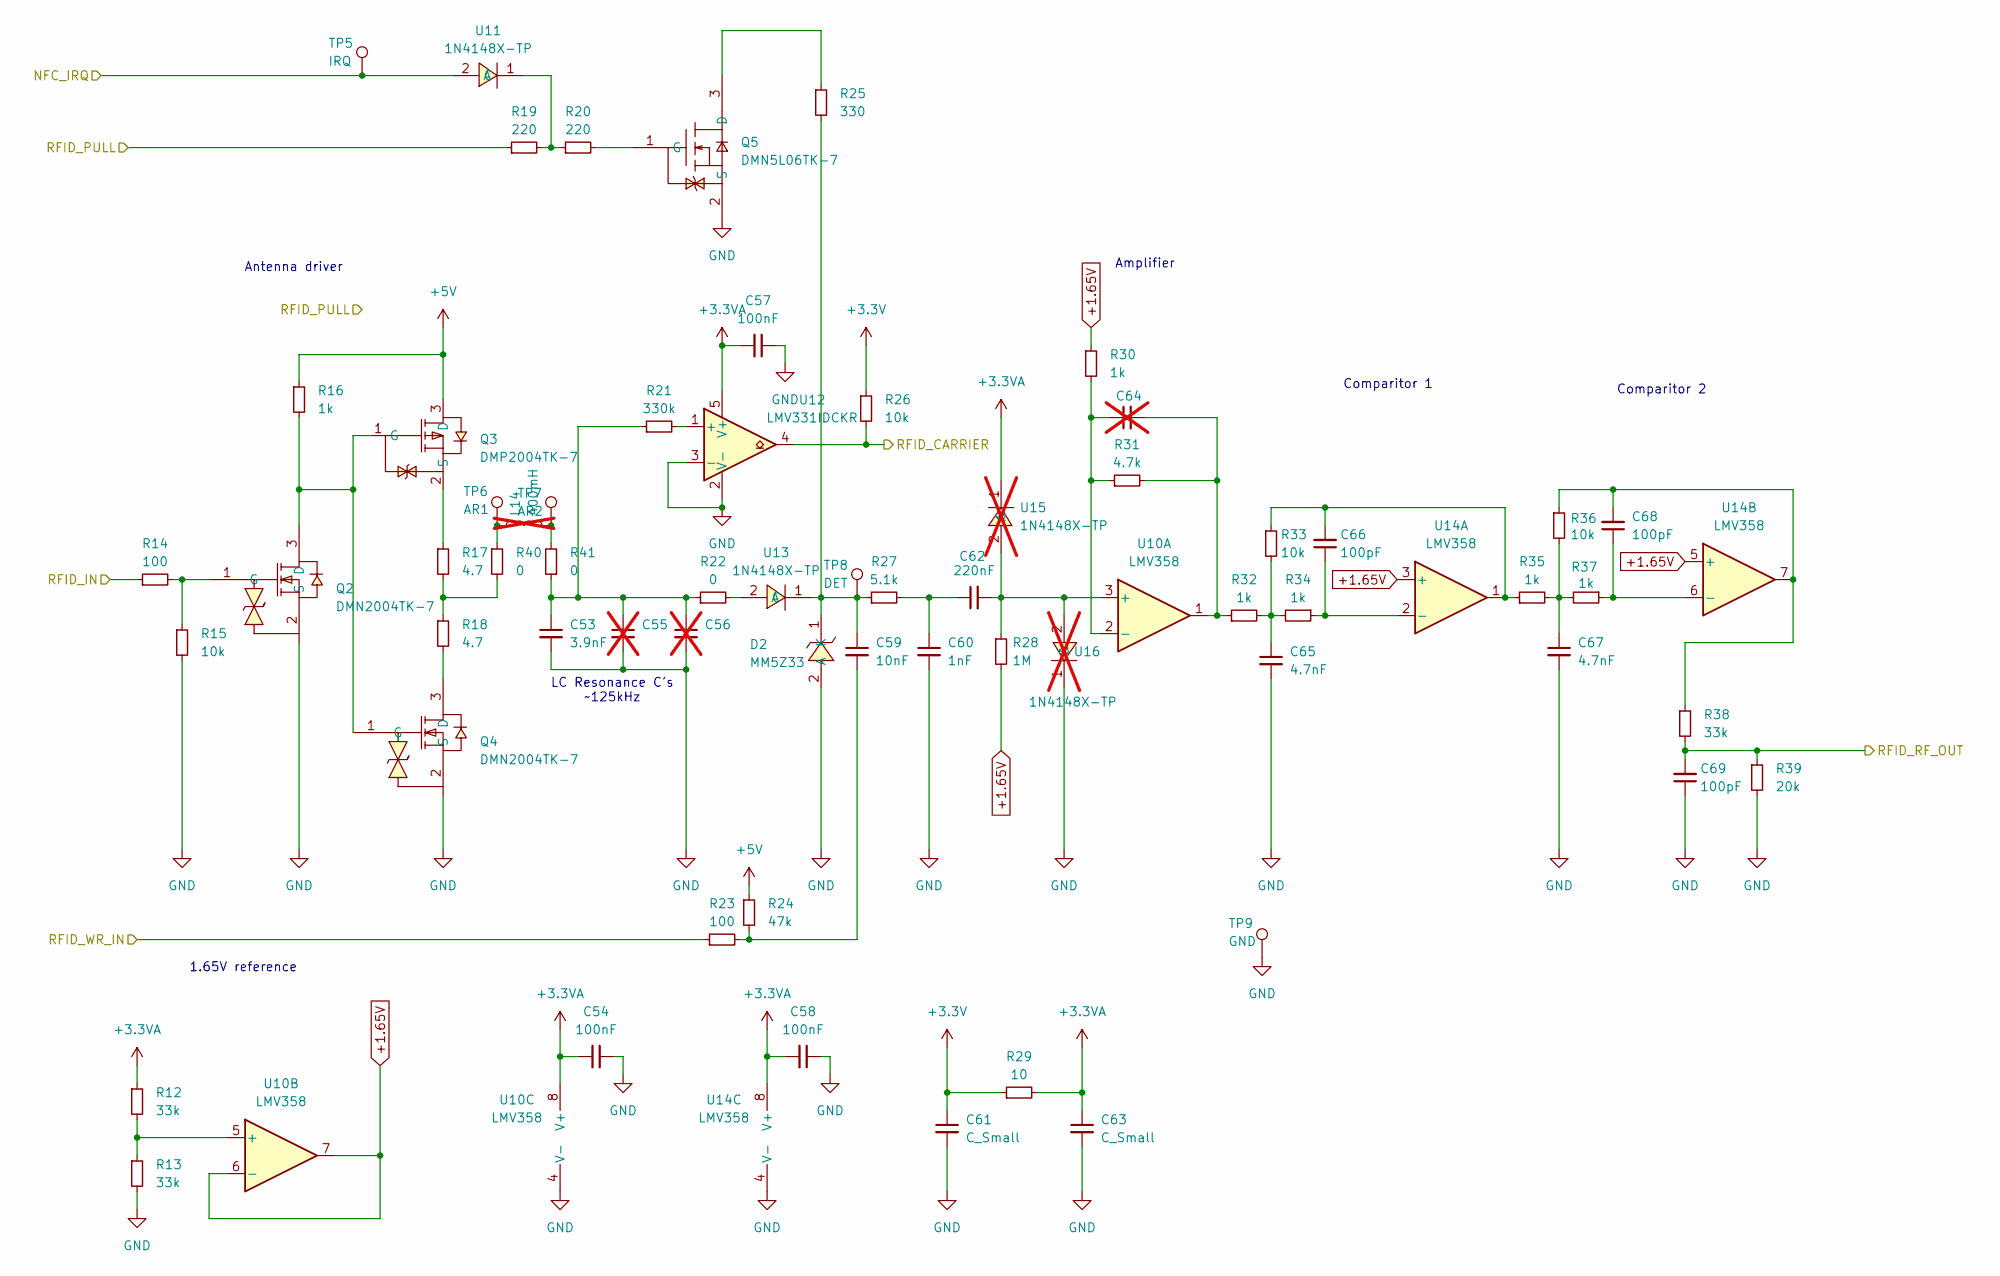
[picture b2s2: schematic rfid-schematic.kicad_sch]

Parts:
C53: 3.9nF; C_0805_2012Metric; LCSC C520026
C54, C57, C58: 100nF; C_0402_1005Metric; LCSC C5448844
C55, C56: C_0805_2012Metric; not fitted
C59: 10nF; C_0402_1005Metric; LCSC C15195
C60: 1nF; C_0402_1005Metric; LCSC C46653
C61, C63: C_Small; R_0603_1608Metric; LCSC C15849
C62: 220nF; C_0402_1005Metric; LCSC C16772
C64: C_0402_1005Metric; not fitted
C65, C67: 4.7nF; C_0402_1005Metric; LCSC C1538
C66, C68, C69: 100pF; C_0402_1005Metric; LCSC C1546
D2: MM5Z33; SOD-523_L1.2-W0.8-LS1.6-RD; LCSC Part C2832591
L14: 400mH; 61-42-rfid-coil; not fitted
Q2, Q4: DMN2004TK-7; SOT-523-3_L1.6-W0.8-P1.00-LS1.6-BR; LCSC Part C460991
Q3: DMP2004TK-7; SOT-523-3_L1.6-W0.8-P1.00-LS1.6-BR; LCSC Part C461051
Q5: DMN5L06TK-7; SOT-523-3_L1.6-W0.8-P1.00-LS1.6-BR; LCSC Part C145111
R12, R13, R38: 33k; C_0402_1005Metric; LCSC C25779
R14: 100; R_0402_1005Metric; LCSC C25076
R15, R26, R33, R36: 10k; R_0402_1005Metric; LCSC C25744
R16, R30, R32, R34, R35, R37: 1k; R_0402_1005Metric; LCSC C11702
R17, R18: 4.7; R_0603_1608Metric; LCSC C325715
R19, R20: 220; R_0402_1005Metric; LCSC C25091
R21: 330k; R_0603_1608Metric; LCSC C23137
R22, R40, R41: 0; R_0402_1005Metric; LCSC C17168
R23: 100; R_0603_1608Metric; LCSC C23197
R24: 47k; R_0402_1005Metric; LCSC C25792
R25: 330; R_0402_1005Metric; LCSC C25104
R27: 5.1k; R_0402_1005Metric; LCSC C25905
R28: 1M; R_0402_1005Metric; LCSC C26083
R29: 10; R_0603_1608Metric; LCSC C22859
R31: 4.7k; R_0402_1005Metric; LCSC C25900
R39: 20k; R_0402_1005Metric; LCSC C25765
TP5: IRQ; TestPoint_Pad_1.0x1.0mm
TP6: AR1; TestPoint_Pad_1.0x1.0mm
TP7: AR2; TestPoint_Pad_1.0x1.0mm
TP8: DET; TestPoint_Pad_1.0x1.0mm
TP9: GND; TestPoint_Pad_1.0x1.0mm
U10, U14: LMV358; VSSOP-8_3x3mm_P0.65mm; LCSC C408974
U11, U13: 1N4148X-TP; SOD-523F_L1.2-W0.8-LS1.7-RD; LCSC Part C507292
U12: LMV331IDCKR; SOT-353_SC-70-5; LCSC C7976
U15, U16: 1N4148X-TP; SOD-523F_L1.2-W0.8-LS1.7-RD; LCSC Part C507292; not fitted

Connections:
+1.65V: R28.2, R30.1, U10.6 (-), U10.7, U14.3 (+), U14.5 (+)
+3.3V: C61.1, R26.1, R29.1; also elsewhere on the board
+3.3VA: C54.2, C57.2, C58.2, C63.1, R12.1, R29.2, U10.8 (V+), U12.5 (V+), U14.8 (V+), U15.1 (C)
+5V: Q3.3 (D), R16.1, R24.1
GND: C53.2, C54.1, C55.2, C56.2, C57.1, C58.1, C60.2, C61.2, C63.2, C65.2, C67.2, C69.1, D2.2 (A), Q2.2 (S), Q4.2 (S), Q5.2 (S), R13.2, R15.2, R39.2, TP9.1, U10.4 (V-), U12.2 (V-), U12.3 (-), U14.4 (V-), U16.1 (C); also elsewhere on the board
NFC_IRQ: TP5.1, U11.2 (A); also elsewhere on the board
unnamed: C53.1, C55.1, C56.1, R21.1, R22.1, R41.1
unnamed: C59.2, R23.2, R24.2
unnamed: C60.1, C62.1, R27.2
unnamed: C64.2, R31.2, R32.1, U10.1
unnamed: C65.1, R32.2, R33.2, R34.2
unnamed: C66.2, R33.1, R35.1, U14.1
unnamed: C67.1, R35.2, R36.2, R37.2
unnamed: C68.2, R36.1, R38.1, U14.7
unnamed: C59.1, D2.1 (K), R25.2, R27.1, TP8.1, U13.1 (C)
unnamed: L14.1, R40.1, TP6.1
unnamed: L14.2, R41.2, TP7.1
unnamed: Q2.3 (D), Q3.1 (G), Q4.1 (G), R16.2
unnamed: Q2.1 (G), R14.2, R15.1
unnamed: Q3.2 (S), R17.1
unnamed: Q4.3 (D), R18.2
unnamed: Q5.3 (D), R25.1
unnamed: Q5.1 (G), R20.2
unnamed: R17.2, R18.1, R40.2
unnamed: C62.2, R28.1, U10.3 (+), U15.2 (A), U16.2 (A)
unnamed: C64.1, R30.2, R31.1, U10.2 (-)
unnamed: R12.2, R13.1, U10.5 (+)
unnamed: R19.2, R20.1, U11.1 (C)
unnamed: R21.2, U12.1 (+)
unnamed: R22.2, U13.2 (A)
unnamed: C66.1, R34.1, U14.2 (-)
unnamed: C68.1, R37.1, U14.6 (-)
RFID_CARRIER: R26.2, U12.4; also elsewhere on the board
RFID_IN: R14.1; also elsewhere on the board
RFID_PULL: R19.1; also elsewhere on the board
RFID_RF_OUT: C69.2, R38.2, R39.1; also elsewhere on the board
RFID_WR_IN: R23.1; also elsewhere on the board

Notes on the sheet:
Amplifier
1.65V reference
Comparitor 1
LC Resonance C's ~125kHz
Antenna driver
Comparitor 2

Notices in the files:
devices/nicolai-electronics/tanmatsu/README.md:
Licensing:
Component | Licence
Hardware design (`tanmatsu-hardware`) | **CERN-OHL-P** (permissive)
Mechanical design (`tanmatsu-mechanical`) | **CERN-OHL-P
Launcher firmware | **MIT
Coprocessor firmware | **MIT
Wi-Fi component | **MIT
Radio (C6) firmware | **Apache-2.0
Documentation, template, app-repository | **no licence file
Branding / logos / artwork | **All rights reserved** — explicitly excluded from the hardware licence
That last row matters if you fork the design: the electronics are permissively licensed, but *"all organization names,
